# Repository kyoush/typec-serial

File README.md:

# typec-serial

USB Type-C to serial UART変換基板のKiCadプロジェクト

## 仕様

- ホストPC接続インタフェース: USB Type-C レセプタクル
- UARTデバイス接続インタフェース: 2.54mmピッチ4pinピンヘッダ \
  (実際の通信は、GND, RX, TXだけ使用、残りは3.3V OUTPUT)
- 表示: RX, TXの通信状態をそれぞれLED表示する

## 参考文献

1. じがへるつ, 技術の泉シリーズ　はじめてのType-C電子工作 (株式会社インプレス, 東京, 2024).
2. じがへるつ, 最強FTDIの新定番 USB-シリアルIC大研究, トランジスタ技術 第62巻, 第3号, pp.63-67, (2025).

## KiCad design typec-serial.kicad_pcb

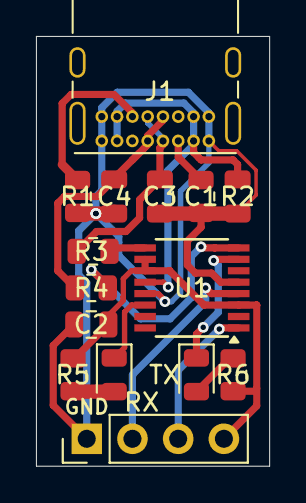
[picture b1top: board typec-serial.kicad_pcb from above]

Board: 2 copper layers, 13.0 x 23.9 mm, 15 parts (0 on the bottom side), 15 nets.

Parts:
C1, C2: 0.1u; C_0805_2012Metric
C3, C4: C; C_0805_2012Metric
GND: Conn_01x04_Pin; PinHeader_1x04_P2.54mm_Vertical
J1: USB4085-GF-A_REVB; USB_C_Receptacle_GCT_USB4085
R1, R2: 5.1k; R_0805_2012Metric
R3, R4: 27; R_0805_2012Metric
R5, R6: 470; R_0805_2012Metric
RX: LED_0805_2012Metric
TX: LED_0805_2012Metric
U1: FT230XS; SSOP-16_3.9x4.9mm_P0.635mm

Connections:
GND: C1.1, C2.1, C3.2, C4.2, GND.1, J1.A1 (GND), J1.A12 (GND__1), J1.B1 (GND__2), J1.B12 (GND__3), R1.2, R2.2, U1.5 (GND), U1.13 (GND)
unnamed: R5.2, RX.2 (A)
unnamed: RX.1 (K), U1.14 (CBUS1)
unnamed: R6.1, TX.2 (A)
unnamed: TX.1 (K), U1.7 (CBUS2)
unnamed: J1.A5 (CC1), R2.1
unnamed: J1.B5 (CC2), R1.1
unnamed: C4.1, J1.A7 (DN1), J1.B7 (DN2), R4.1
unnamed: C3.1, J1.A6 (DP1), J1.B6 (DP2), R3.1
unnamed: C1.2, J1.A4 (VBUS), J1.A9 (VBUS__1), J1.B4 (VBUS__2), J1.B9 (VBUS__3), U1.12 (VCC)
unnamed: GND.2, U1.4 (RXD)
unnamed: GND.3, U1.1 (TXD)
unnamed: C2.2, GND.4, R5.1, R6.2, U1.3 (VCCIO), U1.10 (3V3OUT), U1.11 (~RESET)
unnamed: R3.2, U1.9 (USBDM)
unnamed: R4.2, U1.8 (USBDP)

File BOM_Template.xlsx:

*Reference | *Manufacturer Part number | *QTY | *Original | Description | Purchase Link
C1,C2,C3 | PKMCS0909E4000-R1 | 3 | Y | 0.1u
C4 |  | 1 | Y | 0.47u
D1,D2 |  | 2 | Y
IC1 |  | 1 | Y
R1,R2 |  | 2 | Y | 5.1k
R3,R4 |  | 2 | Y | 27
R5,R6 |  | 2 | Y | 1k
IC1 | NJM12888F33-TE1 | 1 | Y |  | https://www.digikey.jp/ja/products/detail/nisshinbo-micro-de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
U1 | FT230XS-R | 1 | Y |  | https://www.digikey.jp/ja/products/detail/ftdi-future-techno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
J1 | USB4085-GF-A | 1 | Y | NOT ASSEMBLY | https://www.digikey.jp/ja/products/detail/gct/USB4085-GF-A/9859662
Declare：
All ICs will be original even you selected Not original required.
Original: Y means must use the original brand model, N means that you can accep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

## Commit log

2025-03-08 :tada:
2025-03-08 :see_no_evil:
2025-03-08 add BOM
2025-03-08 :rocket: 1st production release
2025-03-10 :fire: remove regulator
2025-03-10 :rocket: 2nd production
